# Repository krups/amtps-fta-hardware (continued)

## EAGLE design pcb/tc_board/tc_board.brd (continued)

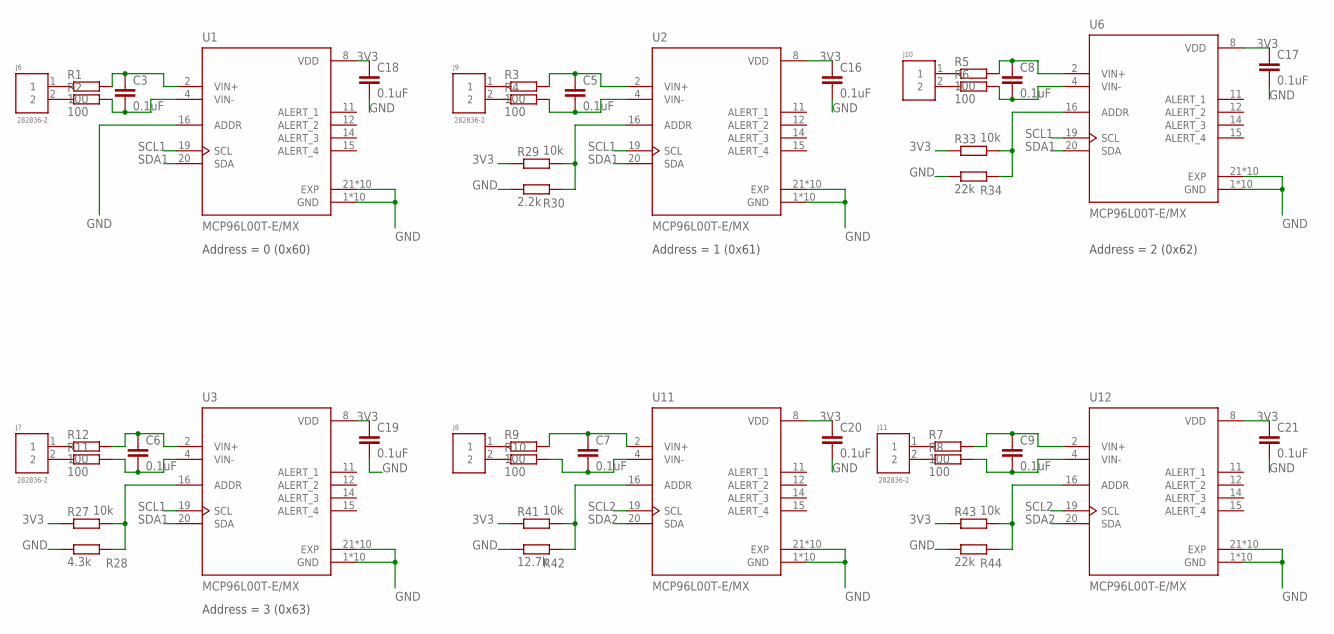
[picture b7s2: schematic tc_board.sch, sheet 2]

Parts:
C3, C5, C6, C7, C8, C9, C16, C17, C18, C19, C20, C21: 0.1uF; C0603
J6, J7, J8, J9, J10, J11: 282836-2; CONN_282836-2
R1, R2, R3, R4, R5, R6, R7, R8, R9, R10, R11, R12: 100; R0603
R27, R29, R33, R41, R43: 10k; R0603
R28: 4.3k; R0603
R30: 2.2k; R0603
R34, R44: 22k; R0603
R42: 12.7k; R0603
U1, U2, U3, U6, U11, U12: MCP96L00T-E/MX; QFN65P500X500X100-21N_MCP96L00T-E/MX

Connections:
3V3: C16.1, C17.1, C18.1, C19.1, C20.1, C21.1, R27.1, R29.1, R33.1, R41.1, R43.1, U1.8 (VDD), U2.8 (VDD), U3.8 (VDD), U6.8 (VDD), U11.8 (VDD), U12.8 (VDD); also elsewhere on the board
GND: C16.2, C17.2, C18.2, C19.2, C20.2, C21.2, R28.1, R30.1, R34.1, R42.1, R44.1, U1.1 (GND), U1.3 (GND), U1.5 (GND), U1.6 (GND), U1.7 (GND), U1.9 (GND), U1.10 (GND), U1.13 (GND), U1.16 (ADDR), U1.17 (GND), U1.18 (GND), U1.21 (EXP), U1.22 (EXP), U1.23 (EXP), U1.24 (EXP), U1.25 (EXP), U1.26 (EXP), U1.27 (EXP), U1.28 (EXP), U1.29 (EXP), U1.30 (EXP), U2.1 (GND), U2.3 (GND), U2.5 (GND), U2.6 (GND), U2.7 (GND), U2.9 (GND), U2.10 (GND), U2.13 (GND), U2.17 (GND), U2.18 (GND), U2.21 (EXP), U2.22 (EXP), U2.23 (EXP), U2.24 (EXP), U2.25 (EXP), U2.26 (EXP), U2.27 (EXP), U2.28 (EXP), U2.29 (EXP), U2.30 (EXP), U3.1 (GND), U3.3 (GND), U3.5 (GND), U3.6 (GND), U3.7 (GND), U3.9 (GND), U3.10 (GND), U3.13 (GND), U3.17 (GND), U3.18 (GND), U3.21 (EXP), U3.22 (EXP), U3.23 (EXP), U3.24 (EXP), U3.25 (EXP), U3.26 (EXP), U3.27 (EXP), U3.28 (EXP), U3.29 (EXP), U3.30 (EXP), U6.1 (GND), U6.3 (GND), U6.5 (GND), U6.6 (GND), U6.7 (GND), U6.9 (GND), U6.10 (GND), U6.13 (GND), U6.17 (GND), U6.18 (GND), U6.21 (EXP), U6.22 (EXP), U6.23 (EXP), U6.24 (EXP), U6.25 (EXP), U6.26 (EXP), U6.27 (EXP), U6.28 (EXP), U6.29 (EXP), U6.30 (EXP), U11.1 (GND), U11.3 (GND), U11.5 (GND), U11.6 (GND), U11.7 (GND), U11.9 (GND), U11.10 (GND), U11.13 (GND), U11.17 (GND), U11.18 (GND), U11.21 (EXP), U11.22 (EXP), U11.23 (EXP), U11.24 (EXP), U11.25 (EXP), U11.26 (EXP), U11.27 (EXP), U11.28 (EXP), U11.29 (EXP), U11.30 (EXP), U12.1 (GND), U12.3 (GND), U12.5 (GND), U12.6 (GND), U12.7 (GND), U12.9 (GND), U12.10 (GND), U12.13 (GND), U12.17 (GND), U12.18 (GND), U12.21 (EXP), U12.22 (EXP), U12.23 (EXP), U12.24 (EXP), U12.25 (EXP), U12.26 (EXP), U12.27 (EXP), U12.28 (EXP), U12.29 (EXP), U12.30 (EXP); also elsewhere on the board
unnamed: J6.1, R1.1
unnamed: J6.2, R2.1
unnamed: J9.1, R3.1
unnamed: J9.2, R4.1
unnamed: J10.1, R5.1
unnamed: J10.2, R6.1
unnamed: J11.1, R7.1
unnamed: J11.2, R8.1
unnamed: J8.1, R9.1
unnamed: J8.2, R10.1
unnamed: J7.2, R11.1
unnamed: J7.1, R12.1
unnamed: C6.1, R12.2, U3.2 (VIN+)
unnamed: C6.2, R11.2, U3.4 (VIN-)
unnamed: C3.2, R2.2, U1.4 (VIN-)
unnamed: C3.1, R1.2, U1.2 (VIN+)
unnamed: C5.1, R3.2, U2.2 (VIN+)
unnamed: C5.2, R4.2, U2.4 (VIN-)
unnamed: C8.1, R5.2, U6.2 (VIN+)
unnamed: C8.2, R6.2, U6.4 (VIN-)
unnamed: C9.1, R7.2, U12.2 (VIN+)
unnamed: C9.2, R8.2, U12.4 (VIN-)
unnamed: C7.2, R10.2, U11.4 (VIN-)
unnamed: C7.1, R9.2, U11.2 (VIN+)
unnamed: R27.2, R28.2, U3.16 (ADDR)
unnamed: R29.2, R30.2, U2.16 (ADDR)
unnamed: R33.2, R34.2, U6.16 (ADDR)
unnamed: R41.2, R42.2, U11.16 (ADDR)
unnamed: R43.2, R44.2, U12.16 (ADDR)
SCL1: U1.19 (SCL), U2.19 (SCL), U3.19 (SCL), U6.19 (SCL); also elsewhere on the board
SCL2: U11.19 (SCL), U12.19 (SCL); also elsewhere on the board
SDA1: U1.20 (SDA), U2.20 (SDA), U3.20 (SDA), U6.20 (SDA); also elsewhere on the board
SDA2: U11.20 (SDA), U12.20 (SDA); also elsewhere on the board

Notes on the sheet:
Address = 0 (0x60)
Address = 1 (0x61)
Address = 2 (0x62)
Address = 3 (0x63)

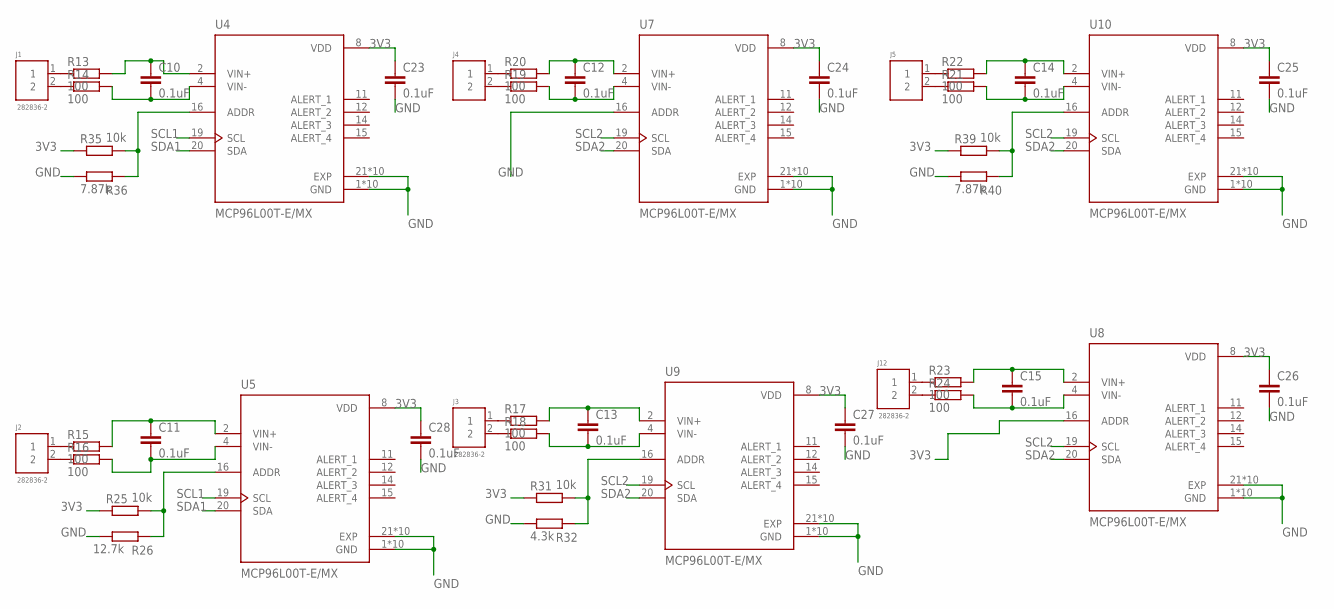
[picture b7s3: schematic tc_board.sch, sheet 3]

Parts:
C10, C11, C12, C13, C14, C15, C23, C24, C25, C26, C27, C28: 0.1uF; C0603
J1, J2, J3, J4, J5, J12: 282836-2; CONN_282836-2
R13, R14, R15, R16, R17, R18, R19, R20, R21, R22, R23, R24: 100; R0603
R25, R31, R35, R39: 10k; R0603
R26: 12.7k; R0603
R32: 4.3k; R0603
R36, R40: 7.87k; R0603
U4, U5, U7, U8, U9, U10: MCP96L00T-E/MX; QFN65P500X500X100-21N_MCP96L00T-E/MX

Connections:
3V3: C23.1, C24.1, C25.1, C26.1, C27.1, C28.1, R25.1, R31.1, R35.1, R39.1, U4.8 (VDD), U5.8 (VDD), U7.8 (VDD), U8.8 (VDD), U8.16 (ADDR), U9.8 (VDD), U10.8 (VDD); also elsewhere on the board
GND: C23.2, C24.2, C25.2, C26.2, C27.2, C28.2, R26.1, R32.1, R36.1, R40.1, U4.1 (GND), U4.3 (GND), U4.5 (GND), U4.6 (GND), U4.7 (GND), U4.9 (GND), U4.10 (GND), U4.13 (GND), U4.17 (GND), U4.18 (GND), U4.21 (EXP), U4.22 (EXP), U4.23 (EXP), U4.24 (EXP), U4.25 (EXP), U4.26 (EXP), U4.27 (EXP), U4.28 (EXP), U4.29 (EXP), U4.30 (EXP), U5.1 (GND), U5.3 (GND), U5.5 (GND), U5.6 (GND), U5.7 (GND), U5.9 (GND), U5.10 (GND), U5.13 (GND), U5.17 (GND), U5.18 (GND), U5.21 (EXP), U5.22 (EXP), U5.23 (EXP), U5.24 (EXP), U5.25 (EXP), U5.26 (EXP), U5.27 (EXP), U5.28 (EXP), U5.29 (EXP), U5.30 (EXP), U7.1 (GND), U7.3 (GND), U7.5 (GND), U7.6 (GND), U7.7 (GND), U7.9 (GND), U7.10 (GND), U7.13 (GND), U7.16 (ADDR), U7.17 (GND), U7.18 (GND), U7.21 (EXP), U7.22 (EXP), U7.23 (EXP), U7.24 (EXP), U7.25 (EXP), U7.26 (EXP), U7.27 (EXP), U7.28 (EXP), U7.29 (EXP), U7.30 (EXP), U8.1 (GND), U8.3 (GND), U8.5 (GND), U8.6 (GND), U8.7 (GND), U8.9 (GND), U8.10 (GND), U8.13 (GND), U8.17 (GND), U8.18 (GND), U8.21 (EXP), U8.22 (EXP), U8.23 (EXP), U8.24 (EXP), U8.25 (EXP), U8.26 (EXP), U8.27 (EXP), U8.28 (EXP), U8.29 (EXP), U8.30 (EXP), U9.1 (GND), U9.3 (GND), U9.5 (GND), U9.6 (GND), U9.7 (GND), U9.9 (GND), U9.10 (GND), U9.13 (GND), U9.17 (GND), U9.18 (GND), U9.21 (EXP), U9.22 (EXP), U9.23 (EXP), U9.24 (EXP), U9.25 (EXP), U9.26 (EXP), U9.27 (EXP), U9.28 (EXP), U9.29 (EXP), U9.30 (EXP), U10.1 (GND), U10.3 (GND), U10.5 (GND), U10.6 (GND), U10.7 (GND), U10.9 (GND), U10.10 (GND), U10.13 (GND), U10.17 (GND), U10.18 (GND), U10.21 (EXP), U10.22 (EXP), U10.23 (EXP), U10.24 (EXP), U10.25 (EXP), U10.26 (EXP), U10.27 (EXP), U10.28 (EXP), U10.29 (EXP), U10.30 (EXP); also elsewhere on the board
unnamed: J1.1, R13.1
unnamed: J1.2, R14.1
unnamed: J12.1, R23.1
unnamed: C10.1, R13.2, U4.2 (VIN+)
unnamed: C10.2, R14.2, U4.4 (VIN-)
unnamed: J2.1, R15.1
unnamed: J2.2, R16.1
unnamed: J3.1, R17.1
unnamed: J3.2, R18.1
unnamed: J4.2, R19.1
unnamed: J4.1, R20.1
unnamed: J5.2, R21.1
unnamed: J5.1, R22.1
unnamed: J12.2, R24.1
unnamed: C12.1, R20.2, U7.2 (VIN+)
unnamed: C12.2, R19.2, U7.4 (VIN-)
unnamed: C15.1, R23.2, U8.2 (VIN+)
unnamed: C14.2, R21.2, U10.4 (VIN-)
unnamed: C15.2, R24.2, U8.4 (VIN-)
unnamed: C14.1, R22.2, U10.2 (VIN+)
unnamed: C13.1, R17.2, U9.2 (VIN+)
unnamed: C13.2, R18.2, U9.4 (VIN-)
unnamed: C11.1, R15.2, U5.2 (VIN+)
unnamed: C11.2, R16.2, U5.4 (VIN-)
unnamed: R25.2, R26.2, U5.16 (ADDR)
unnamed: R31.2, R32.2, U9.16 (ADDR)
unnamed: R35.2, R36.2, U4.16 (ADDR)
unnamed: R39.2, R40.2, U10.16 (ADDR)
SCL1: U4.19 (SCL), U5.19 (SCL); also elsewhere on the board
SCL2: U7.19 (SCL), U8.19 (SCL), U9.19 (SCL), U10.19 (SCL); also elsewhere on the board
SDA1: U4.20 (SDA), U5.20 (SDA); also elsewhere on the board
SDA2: U7.20 (SDA), U8.20 (SDA), U9.20 (SDA), U10.20 (SDA); also elsewhere on the board

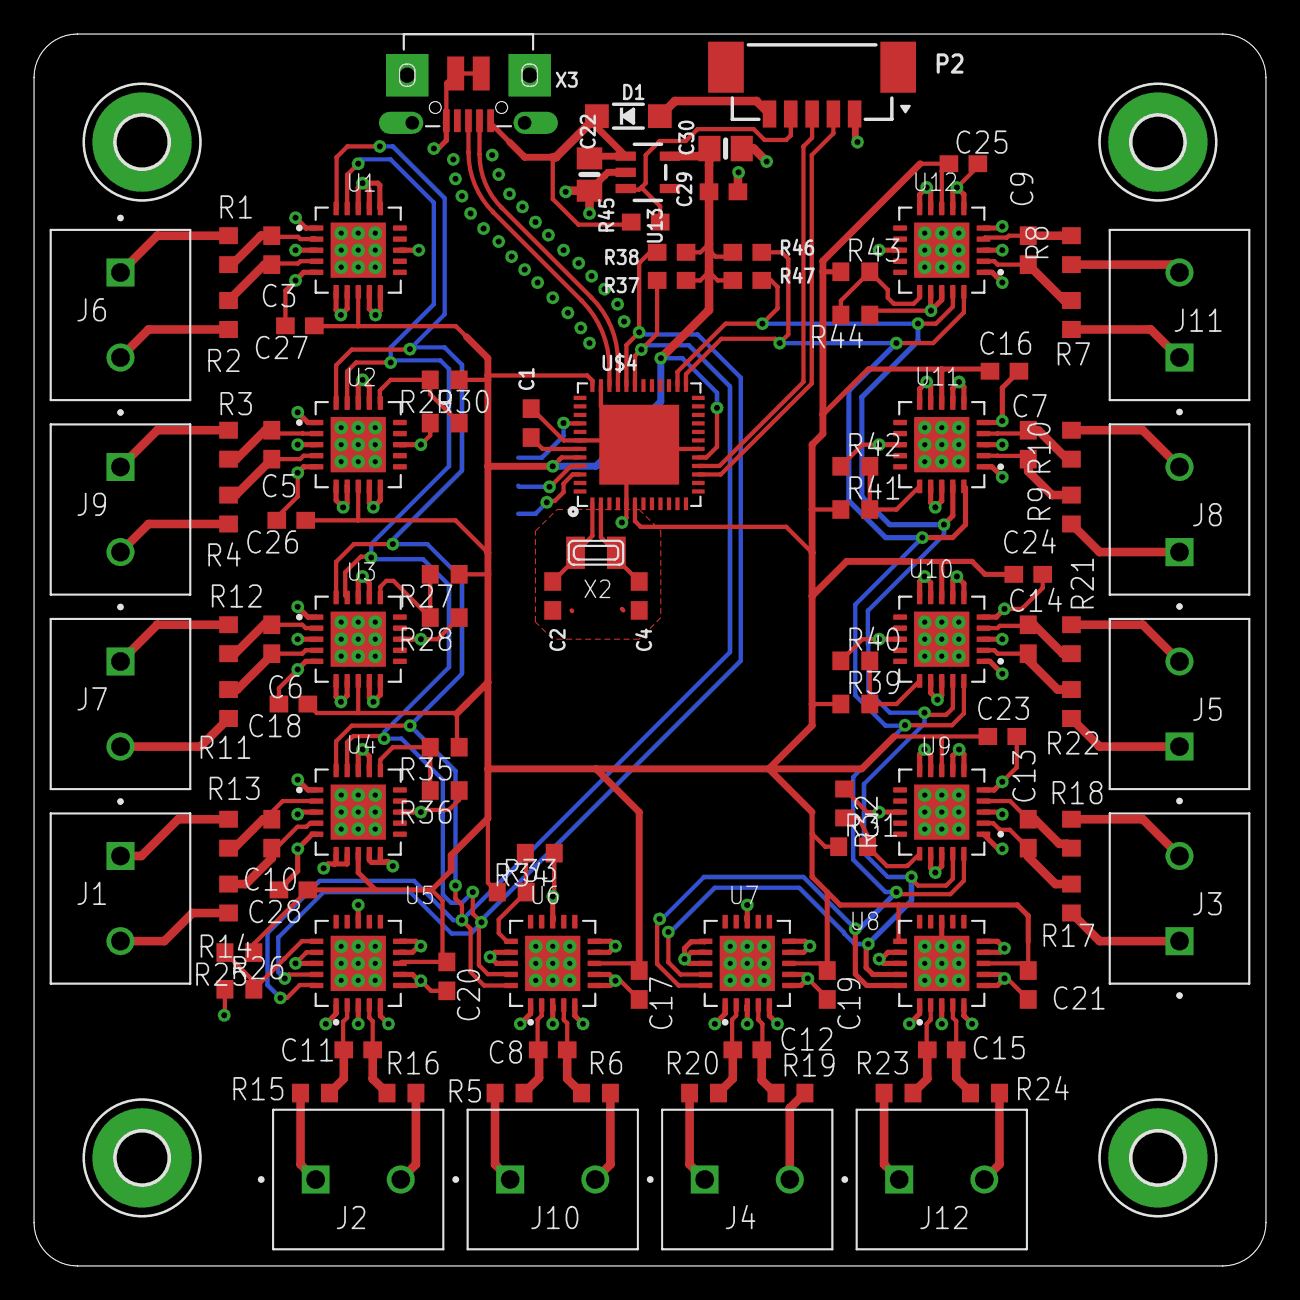
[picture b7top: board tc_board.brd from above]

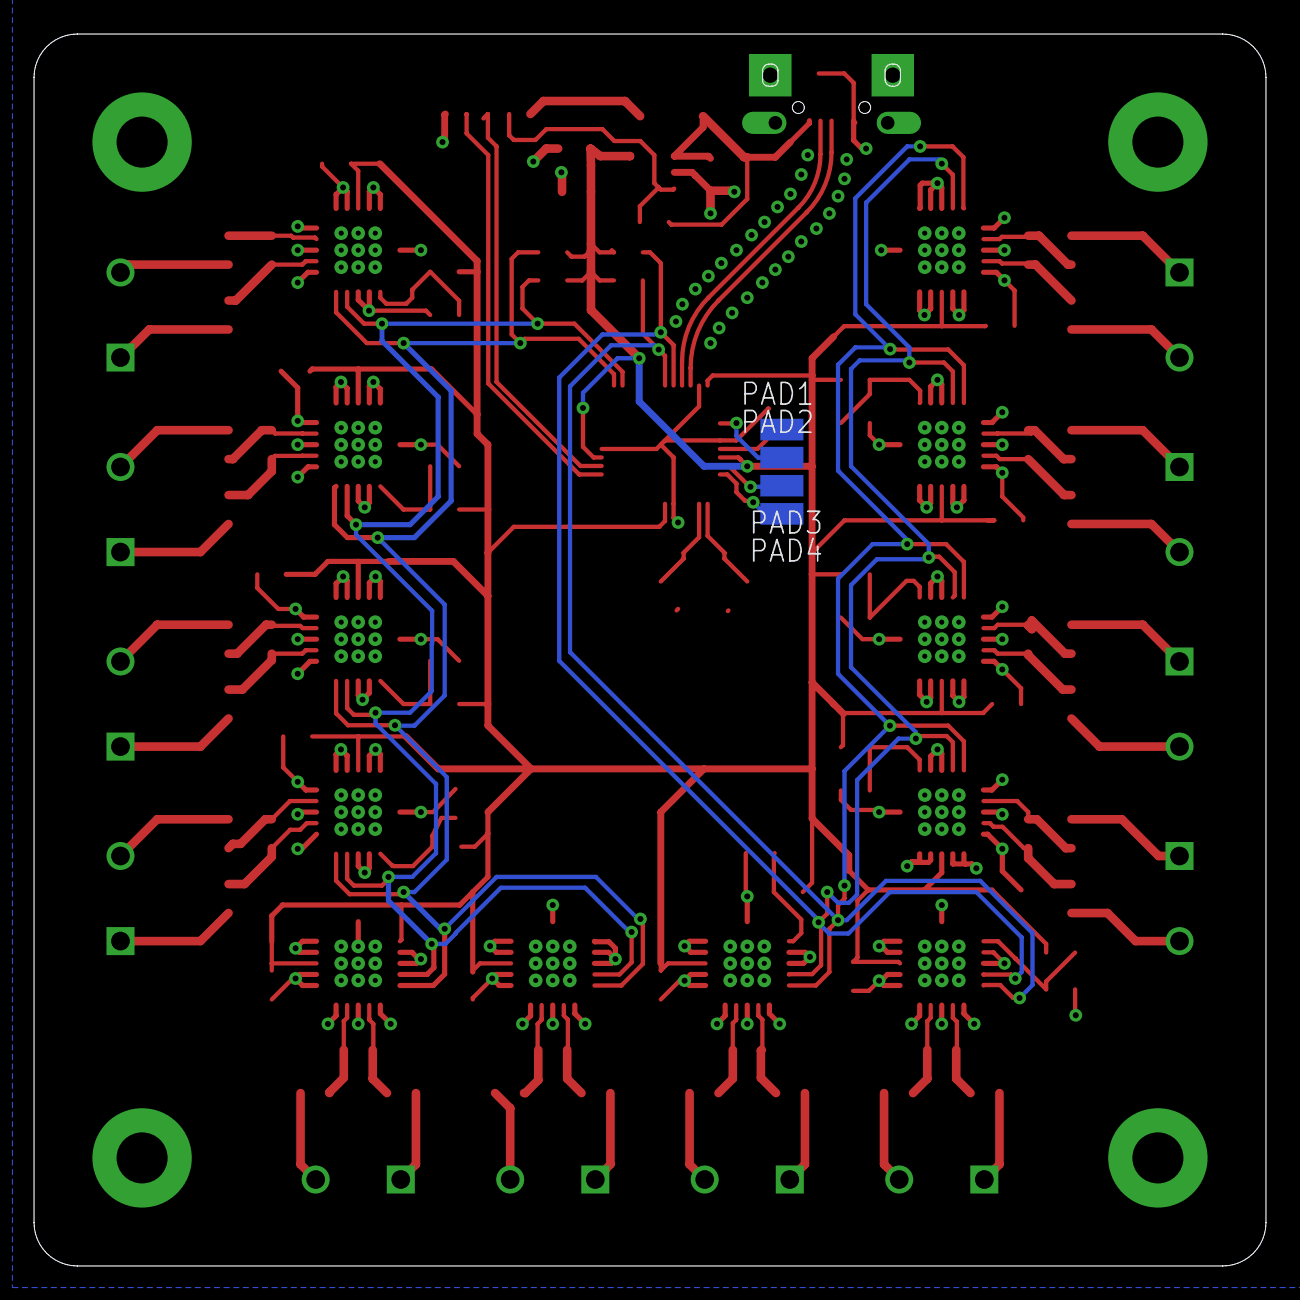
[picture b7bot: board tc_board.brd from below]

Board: 2 copper layers, 72.4 x 72.4 mm, 115 parts (4 on the bottom side), 76 nets.

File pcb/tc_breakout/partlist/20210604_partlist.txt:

Partlist

Exported from tc_breakout.sch at 6/4/21 11:25 AM

EAGLE Version 9.6.2 Copyright (c) 1988-2020 Autodesk, Inc.

Assembly variant: 

Part     Value              Device                    Package                              Library             Sheet

 C10      0.1uF              C-EUC0603                 C0603                                rcl                 1
 C11      0.1uF              C-EUC0603                 C0603                                rcl                 1
 C12      0.1uF              C-EUC0603                 C0603                                rcl                 1
 C13      0.1uF              C-EUC0603                 C0603                                rcl                 1
 C14      0.1uF              C-EUC0603                 C0603                                rcl                 1
 C15      0.1uF              C-EUC0603                 C0603                                rcl                 1
 C22      10µF               CAP_CERAMIC0805-NOOUTLINE 0805-NO                              microbuilder        2
 C23      0.1uF              C-EUC0603                 C0603                                rcl                 1
 C24      0.1uF              C-EUC0603                 C0603                                rcl                 1
 C25      0.1uF              C-EUC0603                 C0603                                rcl                 1
 C26      0.1uF              C-EUC0603                 C0603                                rcl                 1
 C27      0.1uF              C-EUC0603                 C0603                                rcl                 1
 C28      0.1uF              C-EUC0603                 C0603                                rcl                 1
C29      1uF                CAP_CERAMIC0603_NO        0603-NO                              microbuilder        2
C30      10µF               CAP_CERAMIC0805-NOOUTLINE 0805-NO                              microbuilder        2
H1       MOUNT-PAD-ROUND3.0 MOUNT-PAD-ROUND3.0        3,0-PAD                              holes               2
H2       MOUNT-PAD-ROUND3.0 MOUNT-PAD-ROUND3.0        3,0-PAD                              holes               2
H3       MOUNT-PAD-ROUND3.0 MOUNT-PAD-ROUND3.0        3,0-PAD                              holes               2
H4       MOUNT-PAD-ROUND3.0 MOUNT-PAD-ROUND3.0        3,0-PAD                              holes               2
J1       282836-2           282836-2                  CONN_282836-2                        282836-2            1
J2       282836-2           282836-2                  CONN_282836-2                        282836-2            1
J3       282836-2           282836-2                  CONN_282836-2                        282836-2            1
J4       282836-2           282836-2                  CONN_282836-2                        282836-2            1
J5       282836-2           282836-2                  CONN_282836-2                        282836-2            1
J12      282836-2           282836-2                  CONN_282836-2                        282836-2            1
P2       53398-0510         53398-0510                53398-0510                           con-molex-picoblade 2
P3       53398-0410         53398-0410                53398-0410                           con-molex-picoblade 2
  R13      100                R-EU_R0603                R0603                                rcl                 1
  R14      100                R-EU_R0603                R0603                                rcl                 1
  R15      100                R-EU_R0603                R0603                                rcl                 1
  R16      100                R-EU_R0603                R0603                                rcl                 1
 R17      100                R-EU_R0603                R0603                                rcl                 1
 R18      100                R-EU_R0603                R0603                                rcl                 1
 R19      100                R-EU_R0603                R0603                                rcl                 1
 R20      100                R-EU_R0603                R0603                                rcl                 1
 R21      100                R-EU_R0603                R0603                                rcl                 1
 R22      100                R-EU_R0603                R0603                                rcl                 1
 R23      100                R-EU_R0603                R0603                                rcl                 1
 R24      100                R-EU_R0603                R0603                                rcl                 1
  R25      10k                R-EU_R0603                R0603                                rcl                 1
  R26      13k                R-EU_R0603                R0603                                rcl                 1
  R31      10k                R-EU_R0603                R0603                                rcl                 1
  R32      7.5k               R-EU_R0603                R0603                                rcl                 1
  R35      10k                R-EU_R0603                R0603                                rcl                 1
  R36      4.3k               R-EU_R0603                R0603                                rcl                 1
  R39      10k                R-EU_R0603                R0603                                rcl                 1
  R40      2.2k               R-EU_R0603                R0603                                rcl                 1
  R45      100k               RESISTOR_0603_NOOUT       0603-NO                              microbuilder        2
U4       MCP96L00T-E/MX     MCP96L00T-E/MX            QFN65P500X500X100-21N_MCP96L00T-E/MX MCP96L00T-E_MX      1
U5       MCP96L00T-E/MX     MCP96L00T-E/MX            QFN65P500X500X100-21N_MCP96L00T-E/MX MCP96L00T-E_MX      1
U7       MCP96L00T-E/MX     MCP96L00T-E/MX            QFN65P500X500X100-21N_MCP96L00T-E/MX MCP96L00T-E_MX      1
U8       MCP96L00T-E/MX     MCP96L00T-E/MX            QFN65P500X500X100-21N_MCP96L00T-E/MX MCP96L00T-E_MX      1
U9       MCP96L00T-E/MX     MCP96L00T-E/MX            QFN65P500X500X100-21N_MCP96L00T-E/MX MCP96L00T-E_MX      1
U10      MCP96L00T-E/MX     MCP96L00T-E/MX            QFN65P500X500X100-21N_MCP96L00T-E/MX MCP96L00T-E_MX      1
U13      SPX3819-3.3        VREG_SOT23-5              SOT23-5                              microbuilder        2

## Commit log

2021-06-02 first rev of sensor evaluation and documentation
2021-06-02 add project schedule
2021-06-09 add date and rev to manual
2021-06-09 update resistor vals
2021-09-02 added new board models
2021-09-02 add more component cad
2021-10-19 moved to feather wing design
2021-10-19 add imu logger
2021-10-19 add tpms breakout and libraries
2021-10-19 initial versions of imu logger, cdh, and tpms pcb
2021-10-19 added partslists
2021-10-27 updated diagrams and start presentation for jsc visit
2021-10-28 updated presentation and added updated diagrams and images
2021-12-15 finished TPMS board and other updates
2021-12-15 updated main board to have new rs232 transceiver and optional mosfets for pyro and iridium power control
2021-12-15 updated silkscreen and exported cam files for main board
2021-12-15 add some images
2021-12-15 add imu board cam files and replace sd card holder
2022-01-13 documentation update
2022-01-13 add images
2022-02-02 add gimp of v1 board montage
2022-02-02 update documentation adding further schedule additions and initial testing matrix
